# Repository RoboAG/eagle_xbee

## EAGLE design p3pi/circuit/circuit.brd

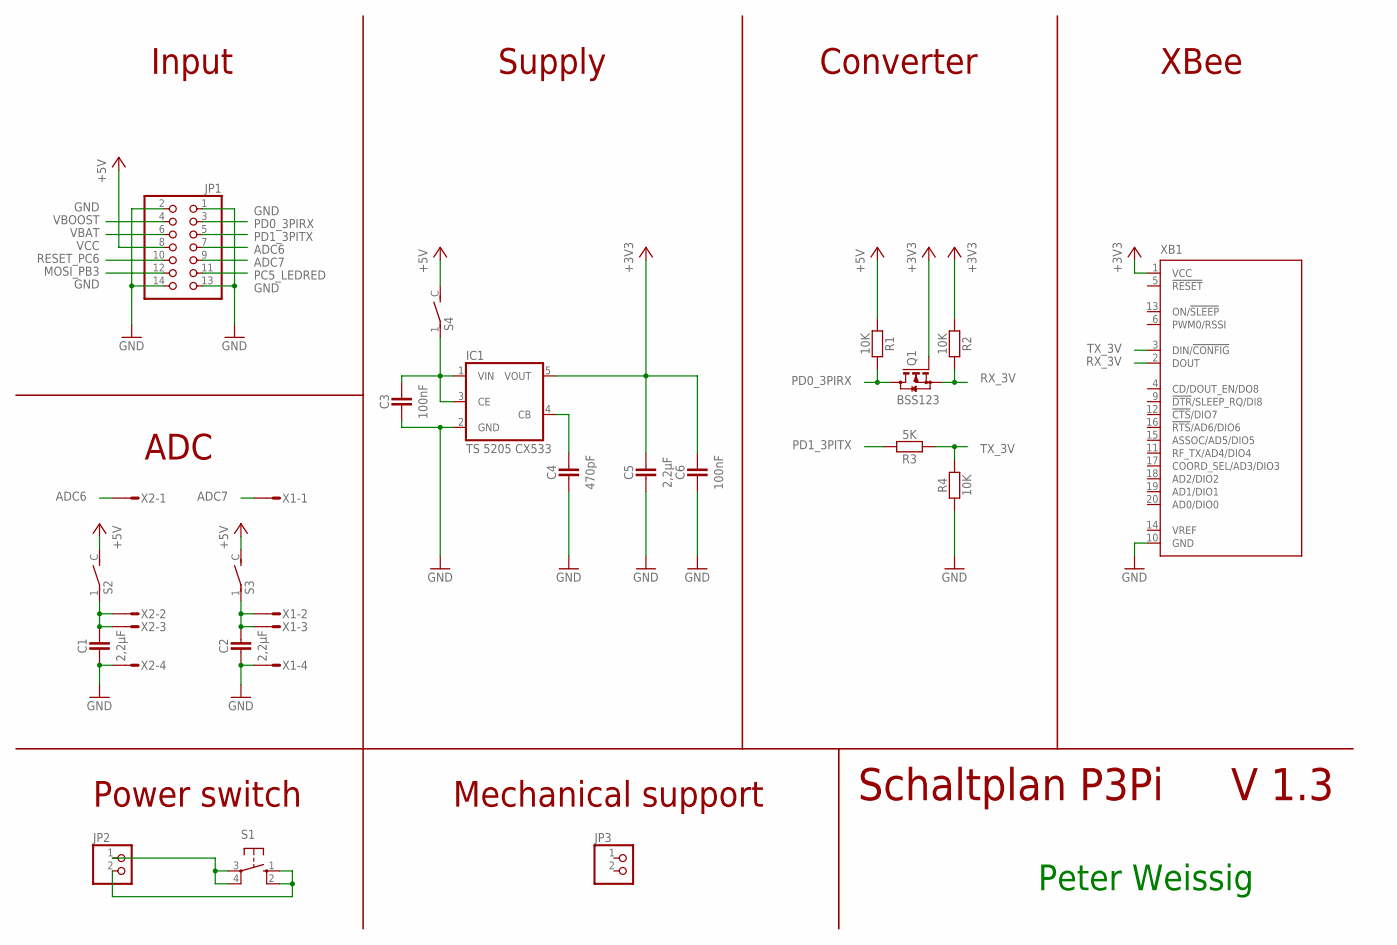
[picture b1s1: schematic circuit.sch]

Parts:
C1, C2, C5: 2,2µF; SMD_1206
C3, C6: 100nF; SMD_1206
C4: 470pF; SMD_1206
IC1: TS 5205 CX533; SOT25
JP1: PINHD-2X7; 2X07
JP2, JP3: PINHD-1X2; 1X02
Q1: BSS123; SOT23
R1, R2, R4: 10K; SMD_1206
R3: 5K; SMD_1206
S1: TASTER; TASTER_SMD
S2, S3, S4: SCHALTER; SCHALTER_SMD
X1, X2: STECKER_MICROMATCH_4SMD
XB1: XBEESMD; FUNK_XBEE_SMD

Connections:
+3V3: C5.1, C6.1, IC1.5 (VOUT), Q1.1 (G), R2.2, XB1.1 (VCC)
ADC6: JP1.7, X2.1
ADC7: JP1.9, X1.1
GND: C1.2, C2.2, C3.2, C4.2, C5.2, C6.2, IC1.2 (GND), JP1.1, JP1.2, JP1.13, JP1.14, R4.2, X1.4, X2.4, XB1.10 (GND)
MOSI_PB3: JP1.12
unnamed: C4.1, IC1.4 (CB)
unnamed: JP2.1, S1.3, S1.4 (P1)
unnamed: JP2.2, S1.1 (S), S1.2 (S1)
PC5_LEDRED: JP1.11
PD0_3PIRX: JP1.3, Q1.3 (D), R1.1
PD1_3PITX: JP1.5, R3.1
RESET_PC6: JP1.10
RX_3V: Q1.2 (S), R2.1, XB1.2 (DOUT)
TX_3V: R3.2, R4.1, XB1.3 (DIN/!CONFIG)
VBAT: JP1.6
VBOOST: JP1.4
VCC: JP1.8, R1.2, S2.C (2), S3.C (2), S4.C (2)
VCC_ADC6: C1.1, S2.1, X2.2, X2.3
VCC_ADC7: C2.1, S3.1, X1.2, X1.3
VCC_XBEE: C3.1, IC1.1 (VIN), IC1.3 (CE), S4.1

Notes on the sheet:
Input
Schaltplan P3Pi
Peter Weissig
V 1.3
Supply
XBee
Converter
Power switch
Mechanical support
ADC

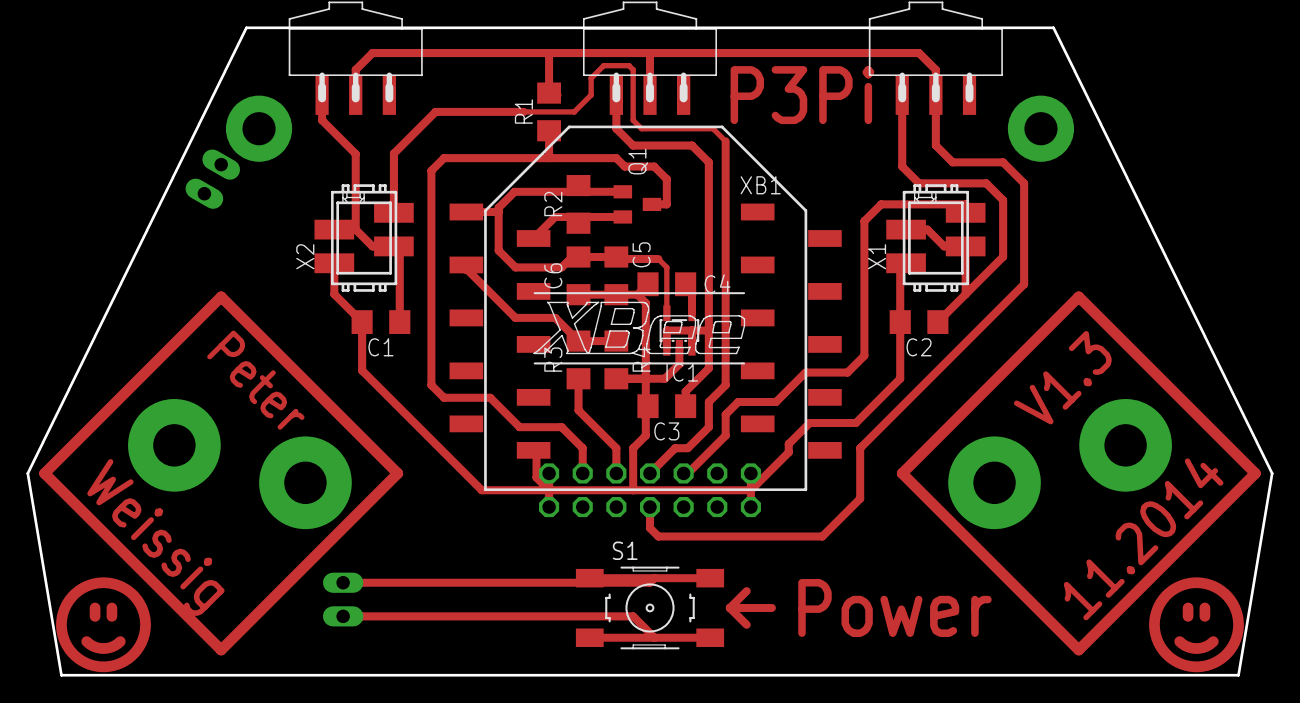
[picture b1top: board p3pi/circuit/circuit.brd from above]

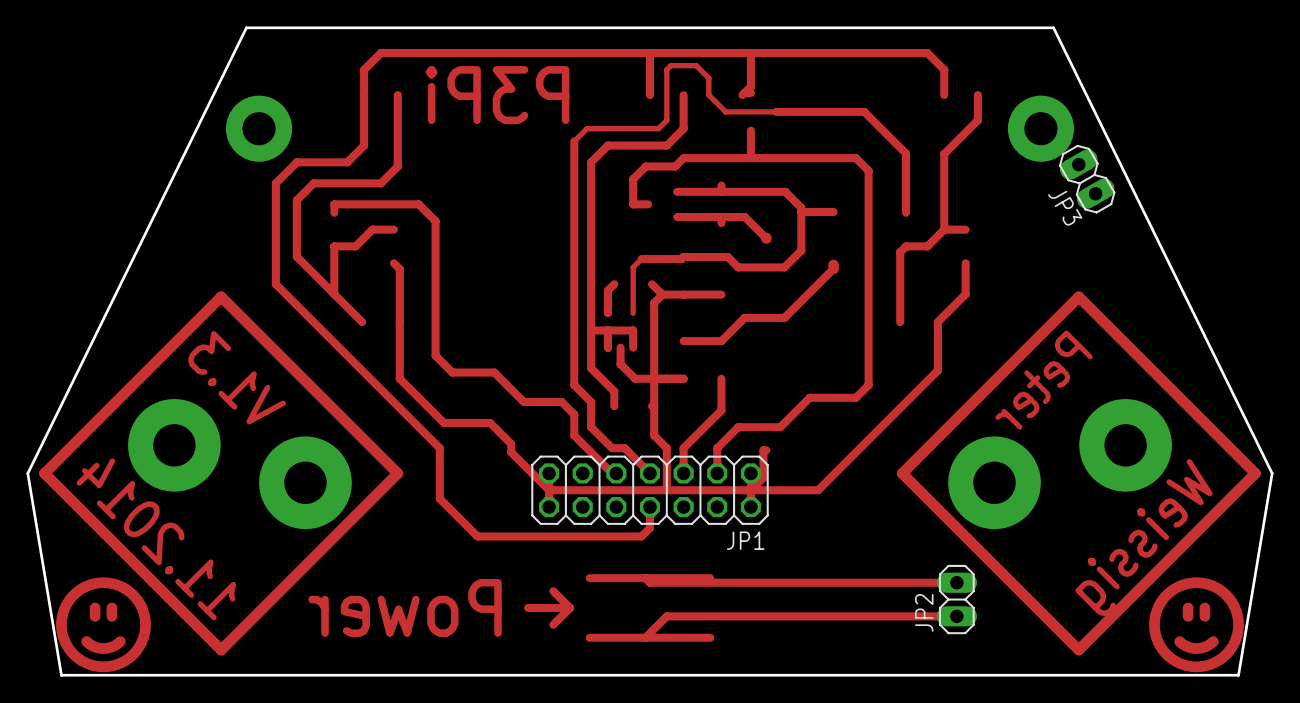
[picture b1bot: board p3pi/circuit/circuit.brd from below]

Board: 2 copper layers, 94.0 x 48.9 mm, 22 parts (3 on the bottom side), 15 nets.

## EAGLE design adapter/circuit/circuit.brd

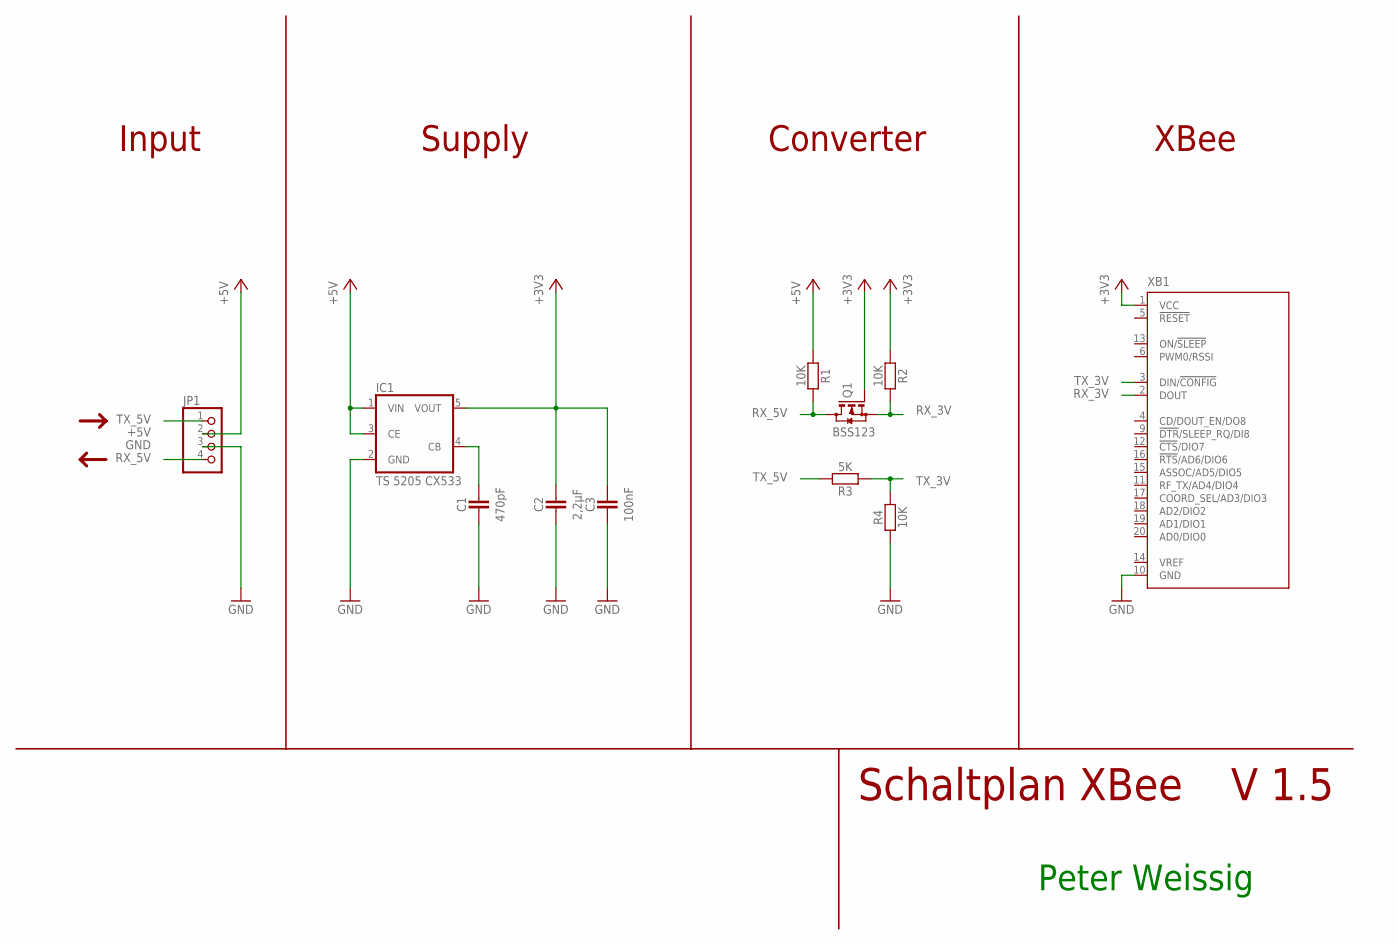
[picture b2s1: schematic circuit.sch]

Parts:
C1: 470pF; SMD_1206
C2: 2,2µF; SMD_1206
C3: 100nF; SMD_1206
IC1: TS 5205 CX533; SOT25
JP1: PINHD-1X4; 1X04
Q1: BSS123; SOT23
R1, R2, R4: 10K; SMD_1206
R3: 5K; SMD_1206
XB1: XBEESMD; FUNK_XBEE2

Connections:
+3V3: C2.1, C3.1, IC1.5 (VOUT), Q1.1 (G), R2.2, XB1.1 (VCC)
+5V: IC1.1 (VIN), IC1.3 (CE), JP1.2, R1.2
GND: C1.2, C2.2, C3.2, IC1.2 (GND), JP1.3, R4.2, XB1.10 (GND)
unnamed: C1.1, IC1.4 (CB)
RX_3V: Q1.2 (S), R2.1, XB1.2 (DOUT)
RX_5V: JP1.4, Q1.3 (D), R1.1
TX_3V: R3.2, R4.1, XB1.3 (DIN/!CONFIG)
TX_5V: JP1.1, R3.1

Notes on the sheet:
Input
Schaltplan XBee
Peter Weissig
V 1.5
Supply
XBee
Converter

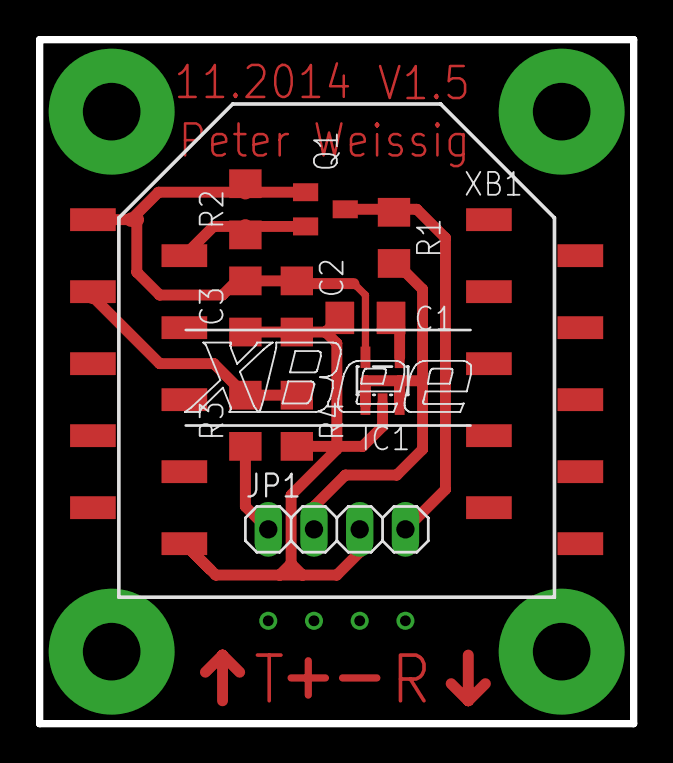
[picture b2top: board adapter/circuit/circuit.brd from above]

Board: 2 copper layers, 33.0 x 38.0 mm, 11 parts (0 on the bottom side), 8 nets.

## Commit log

2015-09-28 add p3pi Version 1.2
